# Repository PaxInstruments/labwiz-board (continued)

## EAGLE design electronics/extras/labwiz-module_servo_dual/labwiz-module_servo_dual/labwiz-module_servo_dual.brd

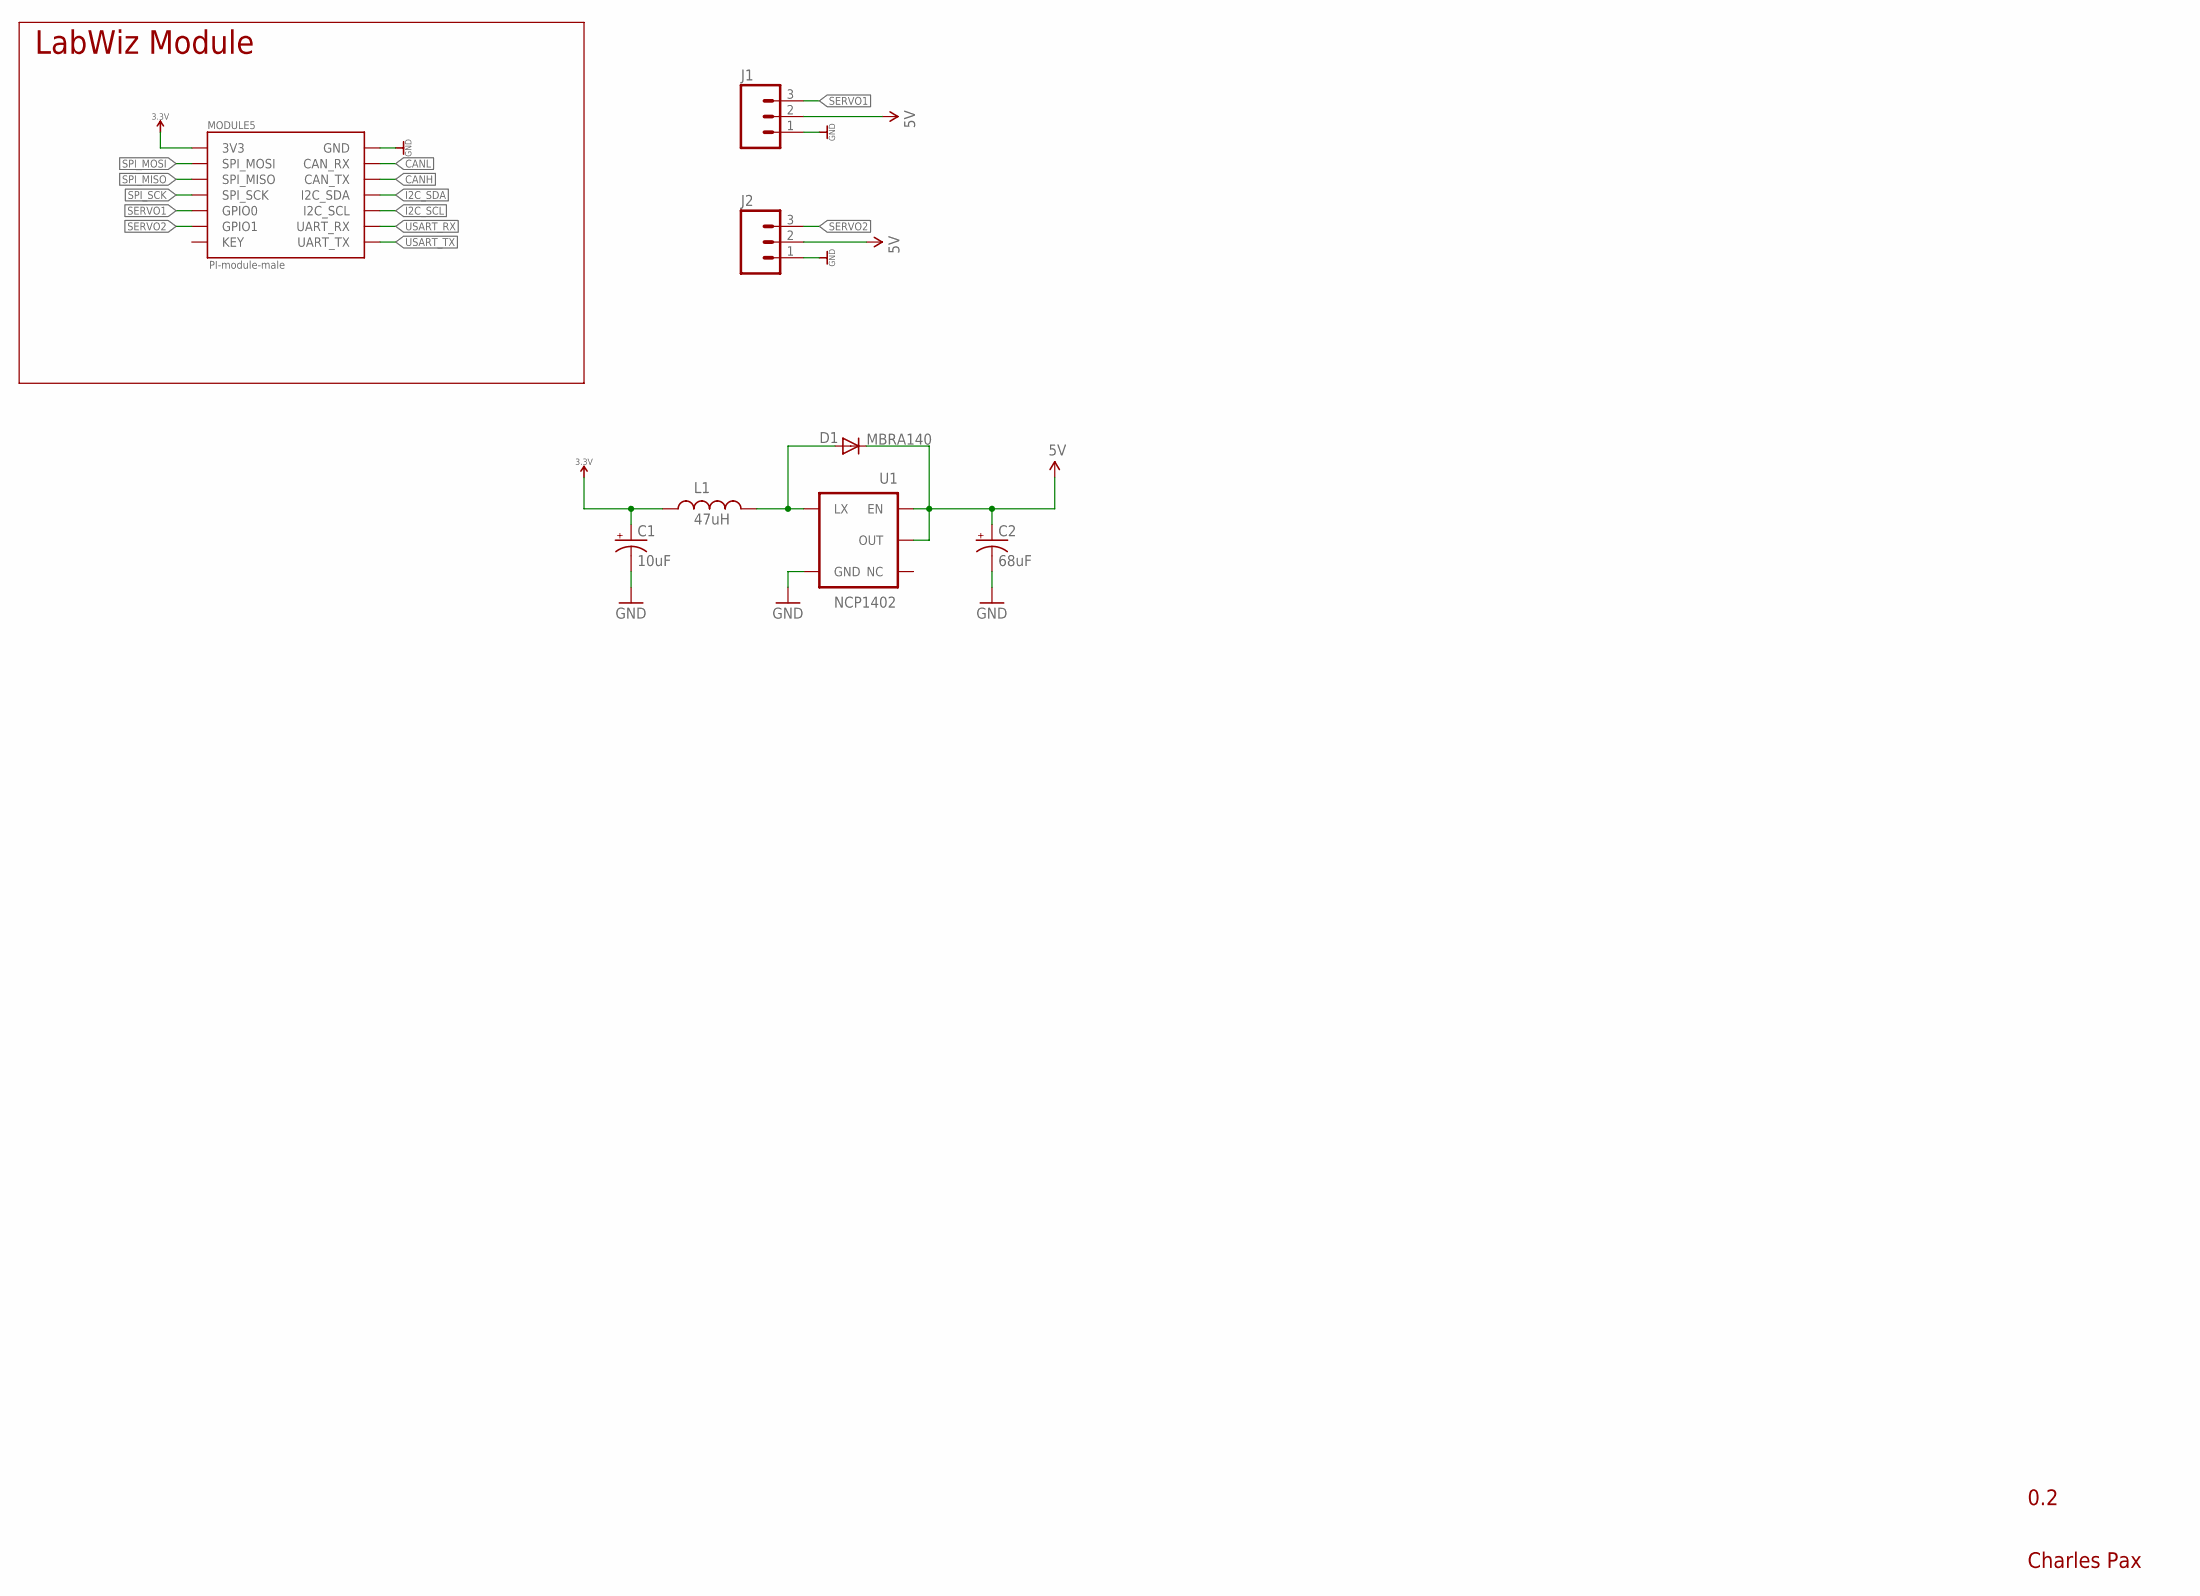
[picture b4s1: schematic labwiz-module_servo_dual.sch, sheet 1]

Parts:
C1: 10uF; EIA3216
C2: 68uF; EIA3528
D1: MBRA140; SMA-DIODE
J1, J2: M031X03_SMD_RA_MALE_POST_SMALLEST; 1X03_SMD_RA_MALE_POST_SMALLEST
L1: 47uH; CR54
MODULE5: PI-module-male; M07X2_2MM_EDGE
U1: NCP1402; SOT23-5

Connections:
3.3V: C1.A (+), L1.P$1 (1), MODULE5.P$13 (3V3)
5V: C2.A (+), D1.C, J1.2, J2.2, U1.1 (EN), U1.2 (OUT)
CANH: MODULE5.P$10 (CAN_TX)
CANL: MODULE5.P$12 (CAN_RX)
GND: C1.C (-), C2.C (-), J1.1, J2.1, MODULE5.P$14 (GND), U1.4 (GND)
I2C_SCL: MODULE5.P$6 (I2C_SCL)
I2C_SDA: MODULE5.P$8 (I2C_SDA)
unnamed: D1.A, L1.P$2 (2), U1.5 (LX)
SERVO1: J1.3, MODULE5.P$5 (GPIO0)
SERVO2: J2.3, MODULE5.P$3 (GPIO1)
SPI_MISO: MODULE5.P$9 (SPI_MISO)
SPI_MOSI: MODULE5.P$11 (SPI_MOSI)
SPI_SCK: MODULE5.P$7 (SPI_SCK)
USART_RX: MODULE5.P$4 (UART_RX)
USART_TX: MODULE5.P$2 (UART_TX)

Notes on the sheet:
0.2
Charles Pax
LabWiz Module

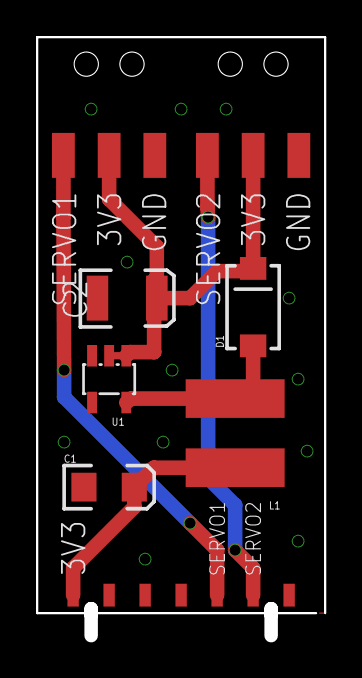
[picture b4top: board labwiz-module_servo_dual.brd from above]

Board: 4 copper layers, 16.0 x 33.2 mm, 8 parts (0 on the bottom side), 6 nets.

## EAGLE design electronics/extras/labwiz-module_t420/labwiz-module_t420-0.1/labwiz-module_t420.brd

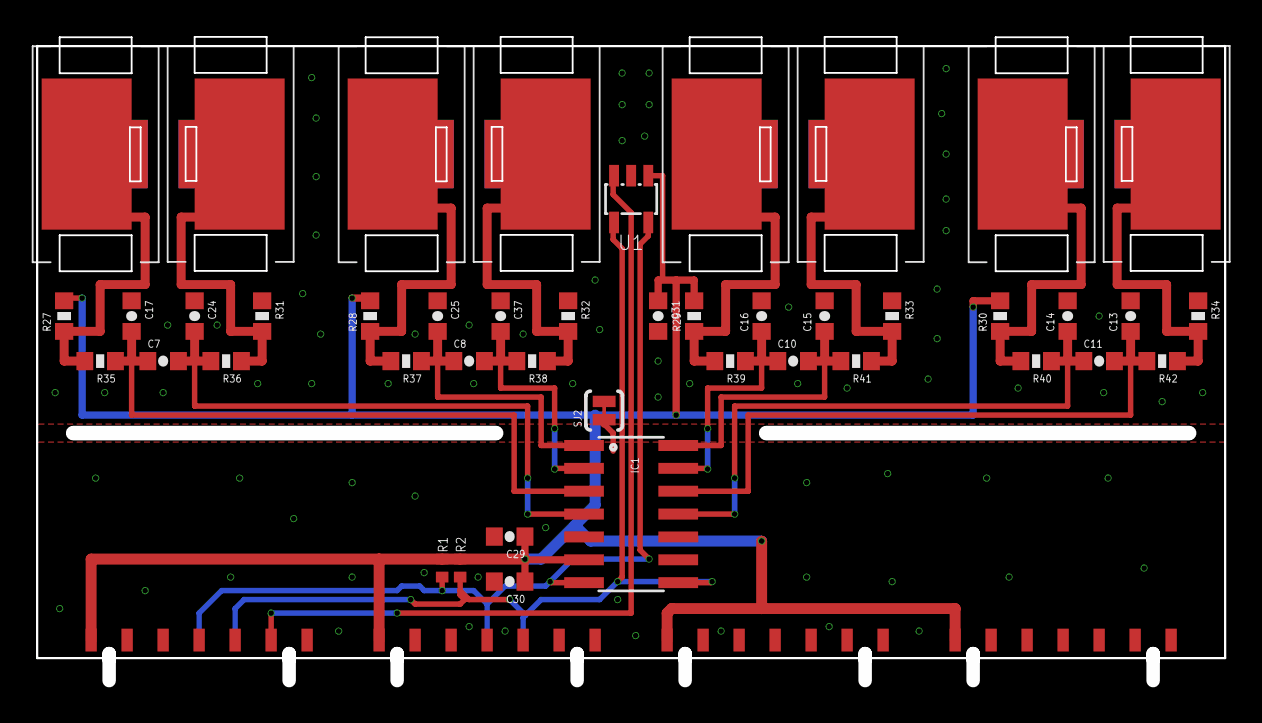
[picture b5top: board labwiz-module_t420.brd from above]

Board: 4 copper layers, 66.0 x 35.8 mm, 48 parts (0 on the bottom side), 22 nets.

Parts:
C7, C8, C10, C11, C30: 1uF; SPARKFUN-CAPACITORS_0603-CAP
C13, C14, C15, C16, C17, C24, C25, C29, C31, C37: 0.1uF; SPARKFUN-CAPACITORS_0603-CAP
IC1: MCP3424; SO14
MODULE5, MODULE6, MODULE7, MODULE8: PI-module-male; M07X2_2MM_EDGE
R1, R2: 1.5k; 0402
R27, R28, R29, R30, R31, R32, R33, R34: 1M; SPARKFUN-RESISTORS_0603-RES
R35, R36, R37, R38, R39, R40, R41, R42: 499R; SPARKFUN-RESISTORS_0603-RES
SJ2: JUMPER-PAD-2-NC_BY_TRACE; PAD-JUMPER-2-NC_BY_TRACE_YES_SILK
U1: MCP9800; SOT23-5L
U$7, U$8, U$9, U$15, U$16, U$17, U$18, U$19: TC-MINI-SINGLE; TC-CLIP-SINGLE

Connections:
3.3V: C29.1, C30.1, C31.1, IC1.6, MODULE5.P$13, MODULE6.P$13, MODULE7.P$13, MODULE8.P$13, R1.1, R2.1, R27.2, R28.2, R29.2, R30.2, U1.1
ALERT: MODULE5.P$3, U1.3
GND: C29.2, C30.2, IC1.5, IC1.9, MODULE5.P$14, MODULE6.P$14, MODULE7.P$14, MODULE8.P$14, SJ2.1
I2C1_SCL: IC1.8, MODULE5.P$6, MODULE6.P$6, R2.2, U1.4
I2C1_SDA: IC1.7, MODULE5.P$8, MODULE6.P$8, R1.2, U1.5
ISOTHERMAL: C13.2, C14.2, C15.2, C16.2, C17.1, C24.1, C25.1, C31.2, C37.1, R31.1, R32.1, R33.1, R34.1, SJ2.2, U1.2
unnamed: R27.1, R35.2, U$7.P$1
unnamed: R32.2, R38.1, U$15.P$1
unnamed: R31.2, R36.1, U$8.P$1
unnamed: R28.1, R37.2, U$9.P$1
unnamed: R30.1, R40.2, U$18.P$1
unnamed: R29.1, R39.2, U$16.P$1
unnamed: R33.2, R41.1, U$17.P$1
unnamed: R34.2, R42.1, U$19.P$1
TC1+: C7.1, C17.2, IC1.3, R35.1
TC1-: C7.2, C24.2, IC1.4, R36.2
TC2+: C8.1, C25.2, IC1.1, R37.1
TC2-: C8.2, C37.2, IC1.2, R38.2
TC3+: C10.1, C16.1, IC1.13, R39.1
TC3-: C10.2, C15.1, IC1.14, R41.2
TC4+: C11.1, C14.1, IC1.11, R40.1
TC4-: C11.2, C13.1, IC1.12, R42.2

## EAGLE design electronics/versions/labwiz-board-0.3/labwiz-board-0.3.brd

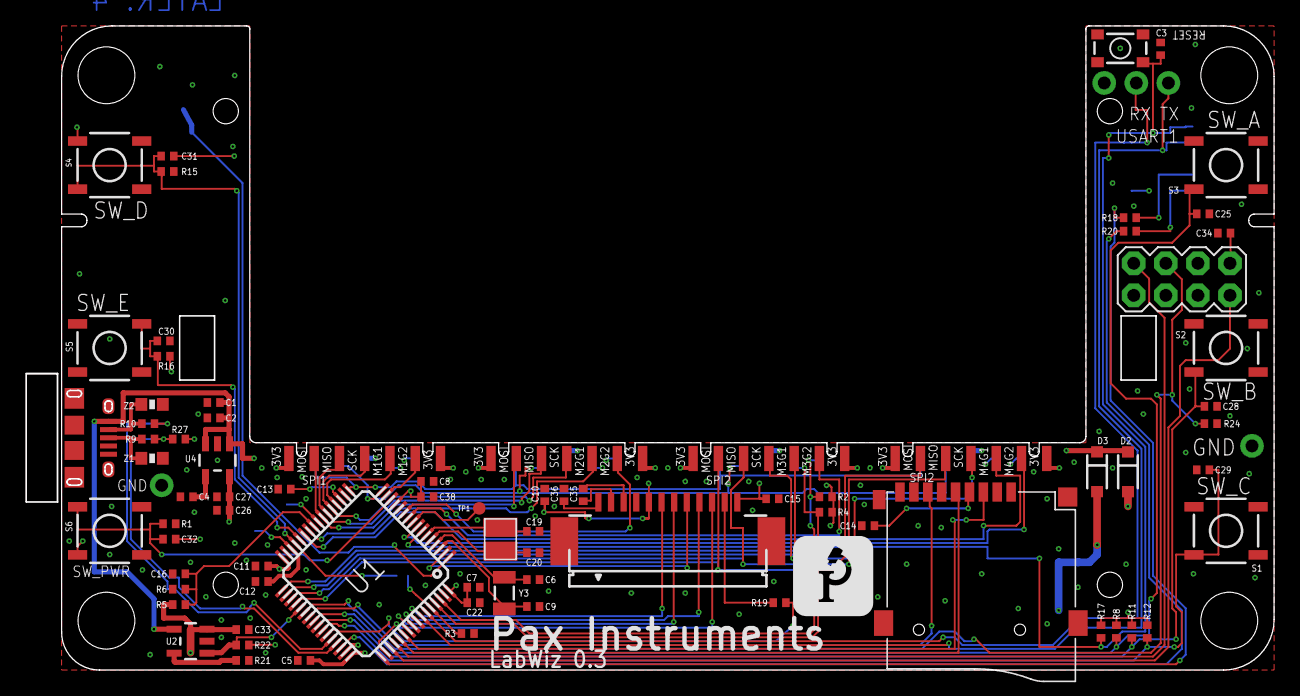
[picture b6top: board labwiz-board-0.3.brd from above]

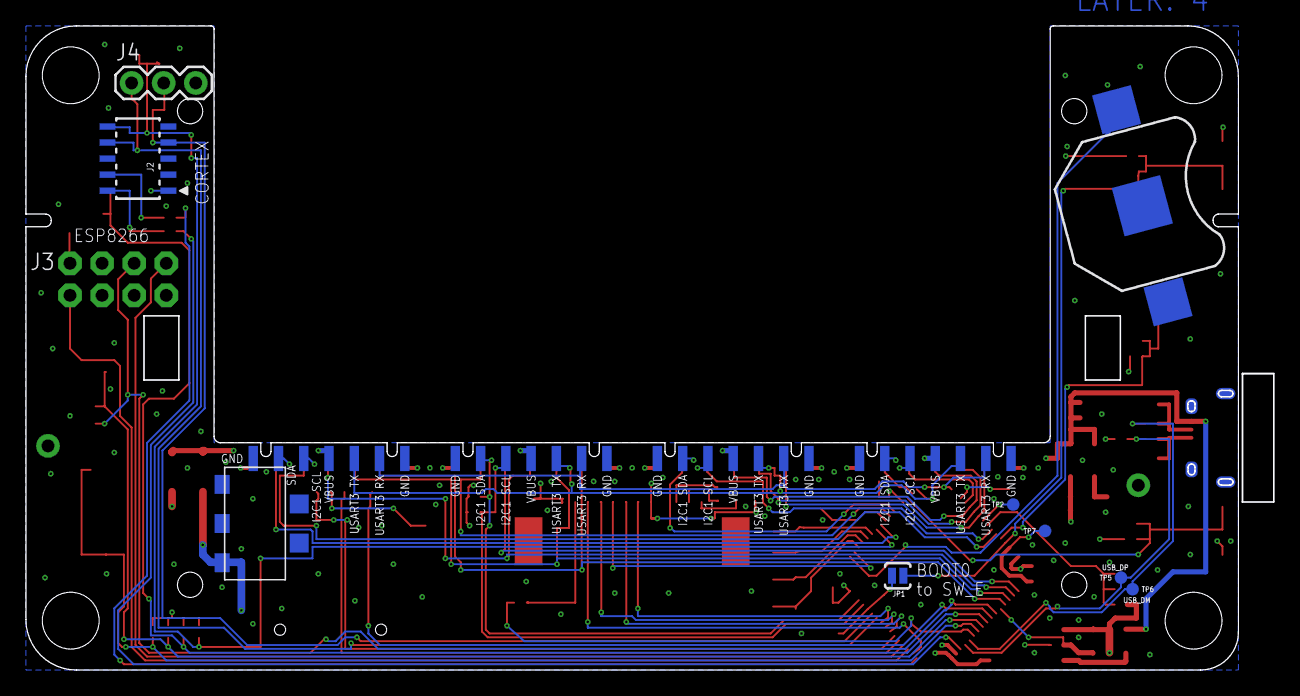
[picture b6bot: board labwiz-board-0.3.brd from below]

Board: 4 copper layers, 98.8 x 51.0 mm, 92 parts (9 on the bottom side), 68 nets.

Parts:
BAT1: BATTCON_12MM
C1, C12, C22: 4.7uF; 0402
C2, C3, C5, C7, C10, C11, C13, C14, C15, C16, C25, C27, C28, C29, C30, C31, C32: 100nF; 0402
C4: 470pF; 0402
C6, C9, C19, C20: 8pF; 0402
C8: 10nF; 0402
C26, C33, C34: 10uF; 0402
C35, C36, C38: 1uF; 0402
D2, D3: 1N4148W; SOD-123
J1: SD_MICRO_SDIO_1BIT; SD_MICRO_1
J2: CORTEX_DEBUGSMD; SAMTECH_FTSH-105-01
J3: DNP; 2X4
J4: 1X03
JP1: DNP; PAD-JUMPER-2-NO_YES_SILK
MODULE1, MODULE2, MODULE3, MODULE4: PI-module-female; M07X2_2MM_EDGE
R1, R3, R5, R6, R8, R11, R12, R15, R16, R17, R21, R22, R24: 10K; 0402
R2, R4, R27: 1.5K; 0402
R9, R10: 22R; 0402
R18, R20: 100R; 0402
R19: 3.3R; 0402
S1, S2, S3, S4, S5, S6: SWITCH-MOMENTARY-2SMD; TACTILE_SWITCH_SMD
S7: SWITCH-MOMENTARY-2SMD-3; TACTILE_SWITCH_SMD-3
TP1, TP2, TP5, TP6, TP7: DNP; PAD_1MM
TP3, TP4: DNP; M01_TH
U1: STM32F10XRXT6; TQFP64
U2: MCP73831; SOT23-5
U4: MIC5219-3.3V; SOT23-5
U$1: USB_MICROSMT+THRUHULE; USB_MICRO_THRUHOLE
U$2: DNP; FOUR_LAYER_WARNING
U$3: LG132643-DG
U$4: BL-XX_BATTERY_7-7; BL-XX-BATTERY
U$6: PAX-LOGO-0.25IN
U$9: 8MHz; NX3225GD
X2: M12_BOTTOM_CONTACTS_FPC_1MM; FPC_12P_1MM
Y3: 32.768kHz; CRYSTAL-SMD-3.2X1.5MM
Z1, Z2: PGB1010603; SPARKFUN-RESISTORS_0603-RES

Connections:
3.3V: C5.1, C7.1, C8.1, C10.2, C11.1, C13.1, C14.2, C15.2, C22.2, C26.2, C27.2, C31.2, C32.2, C34.2, C38.2, D3.A, J1.4, J2.1, J3.8, MODULE1.P$1, MODULE1.P$13, MODULE2.P$1, MODULE2.P$13, MODULE3.P$1, MODULE3.P$13, MODULE4.P$1, MODULE4.P$13, R2.1, R4.1, R8.1, R11.1, R12.1, R16.1, R17.1, R22.2, R27.2, S4.1, S6.3, U1.13, U1.19, U1.32, U1.48, U1.64, U4.5, X2.5, X2.12
BATT_STAT: R22.1, U1.37, U2.1
BOOT0: JP1.2, R3.2, U1.60
D+: R9.1, U$1.PIN$3, Z1.2
D-: R10.1, U$1.PIN$2, Z2.2
GND: BAT1.GND, C1.1, C2.1, C3.2, C4.2, C5.2, C6.2, C7.2, C8.2, C9.2, C10.1, C11.2, C12.1, C13.2, C14.1, C15.1, C16.2, C19.2, C20.2, C22.1, C25.1, C26.1, C27.1, C28.1, C29.1, C30.1, C33.2, C34.1, C36.1, C38.1, J1.6, J1.G1, J1.G2, J1.G3, J1.G4, J2.3, J2.5, J2.9, J3.1, J4.3, MODULE1.P$2, MODULE1.P$14, MODULE2.P$2, MODULE2.P$14, MODULE3.P$2, MODULE3.P$14, MODULE4.P$2, MODULE4.P$14, R1.1, R3.1, R6.1, R15.1, R21.2, R24.2, S1.1, S2.1, S3.1, S5.1, S7.1, TP3.P$1, TP4.P$1, U1.12, U1.18, U1.31, U1.47, U1.63, U2.2, U4.2, U$1.PAD$1, U$1.PAD$2, U$1.PAD$3, U$1.PAD$4, U$1.PAD$5, U$1.PAD$6, U$1.PAD$7, U$1.PAD$8, U$1.PAD$9, U$1.PAD$10, U$1.PIN$5, U$4.P$3, U$4.P$4, U$4.P$5, X2.4, Z1.1, Z2.1
I2C1_SCL: MODULE1.P$10, MODULE2.P$10, MODULE3.P$10, MODULE4.P$10, R4.2, U1.61
I2C1_SDA: MODULE1.P$12, MODULE2.P$12, MODULE3.P$12, MODULE4.P$12, R2.2, U1.62
LCD_A0: U1.2, X2.8
LCD_BL: R19.2, U1.43
LCD_CS: U1.50, X2.10
LCD_MOSI: U1.57, X2.6
LCD_RST: U1.56, X2.9
LCD_SCK: U1.55, X2.7
MOD1_GPIO1: MODULE1.P$9, U1.20
MOD1_GPIO2: MODULE1.P$11, U1.15
MOD2_GPIO1: MODULE2.P$9, U1.26
MOD2_GPIO2: MODULE2.P$11, U1.11
MOD3_GPIO1: MODULE3.P$9, U1.33
MOD3_GPIO2: MODULE3.P$11, U1.10
MOD4_GPIO1: MODULE4.P$9, U1.27
MOD4_GPIO2: MODULE4.P$11, U1.8
unnamed: C4.1, U4.4
unnamed: R19.1, X2.11
unnamed: C35.1, X2.3
unnamed: C35.2, X2.2
unnamed: C36.2, X2.1
unnamed: R21.1, U2.5
NRST: C3.1, J2.10, R17.2, S7.4, U1.7
OSC_IN: C20.1, U1.5, U$9.P$2
OSC_OUT: C19.1, U1.6, U$9.P$1
PC1: TP1.P$1, U1.9
PC4: TP2.P$1, U1.24
RTC_BAT: BAT1.PWR@1, U1.1
RTC_OSC_IN: C9.1, U1.3, Y3.P$2
RTC_OSC_OUT: C6.1, U1.4, Y3.P$1
SDIO_CK: J1.5, U1.53
SDIO_CMD: J1.3, U1.54
SDIO_D0: J1.7, U1.39
SPI1_MISO: MODULE1.P$5, MODULE2.P$5, U1.22
SPI1_MOSI: MODULE1.P$3, MODULE2.P$3, U1.23
SPI1_SCK: MODULE1.P$7, MODULE2.P$7, U1.21
SPI2_MISO: MODULE3.P$5, MODULE4.P$5, U1.35
SPI2_MOSI: MODULE3.P$3, MODULE4.P$3, U1.36
SPI2_SCK: MODULE3.P$7, MODULE4.P$7, U1.34
SWCLK: R18.1, U1.49
SWDCLK_M: J2.4, R18.2
SWDIO: R20.1, U1.46
SWDIO_M: J2.2, R20.2
SW_A: C25.2, R8.2, S3.3, U1.40
SW_B: C28.2, R11.2, S2.3, U1.41
SW_C: C29.2, R12.2, S1.3, U1.42
SW_D_BOOT1: C30.2, R16.2, S5.3, U1.28
SW_E_BOOT0: C31.1, JP1.1, R15.2, S4.3, U1.29
SW_PWR: C32.1, R1.2, S6.1, U1.14
USART1_RX: J2.7, J4.2, U1.59
USART1_TX: J2.8, J4.1, U1.58
USART2_RX: MODULE1.P$4, MODULE2.P$4, MODULE3.P$4, MODULE4.P$4, U1.17
USART2_TX: MODULE1.P$6, MODULE2.P$6, MODULE3.P$6, MODULE4.P$6, U1.16
USART3_RX: J3.2, U1.52
USART3_TX: J3.7, U1.51
USB_DM: R10.2, TP6.P$1, U1.44
USB_DP: R9.2, R27.1, TP5.P$1, U1.45
VBAT: C33.1, D2.A, R5.2, U2.3, U$4.P$1
VBAT_DROP: C16.1, R5.1, R6.2, U1.25
VBUS: C1.2, C2.2, D2.C, D3.C, MODULE1.P$8, MODULE2.P$8, MODULE3.P$8, MODULE4.P$8, U2.4, U4.1, U4.3, U$1.PIN$1
VCAP1: C12.2, TP7.P$1, U1.30
WIFI_EN: J3.4, R24.1, U1.38
